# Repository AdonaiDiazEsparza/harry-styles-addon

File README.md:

# The harry styles Addon
This is a little project created for fun and love, since time ago a met a person who likes Harry Styles and an appreciated present from me is create this addon or badge or PCB as you like to call it.

## Components Hardware

| Component          | Name                 |
|--------------------|----------------------|
| MCU                | Ch32v203c8t6         |
| LiPo Charger       | TP4050/TC4050        | 
| USB Conector       | USB-C 16 pin         |
| BATTERY            | LiPo JST connector   |

## Firmware
By the moment there's no firmware programmed, it is a PoC and when the hardware will be finished, the programming will begin.

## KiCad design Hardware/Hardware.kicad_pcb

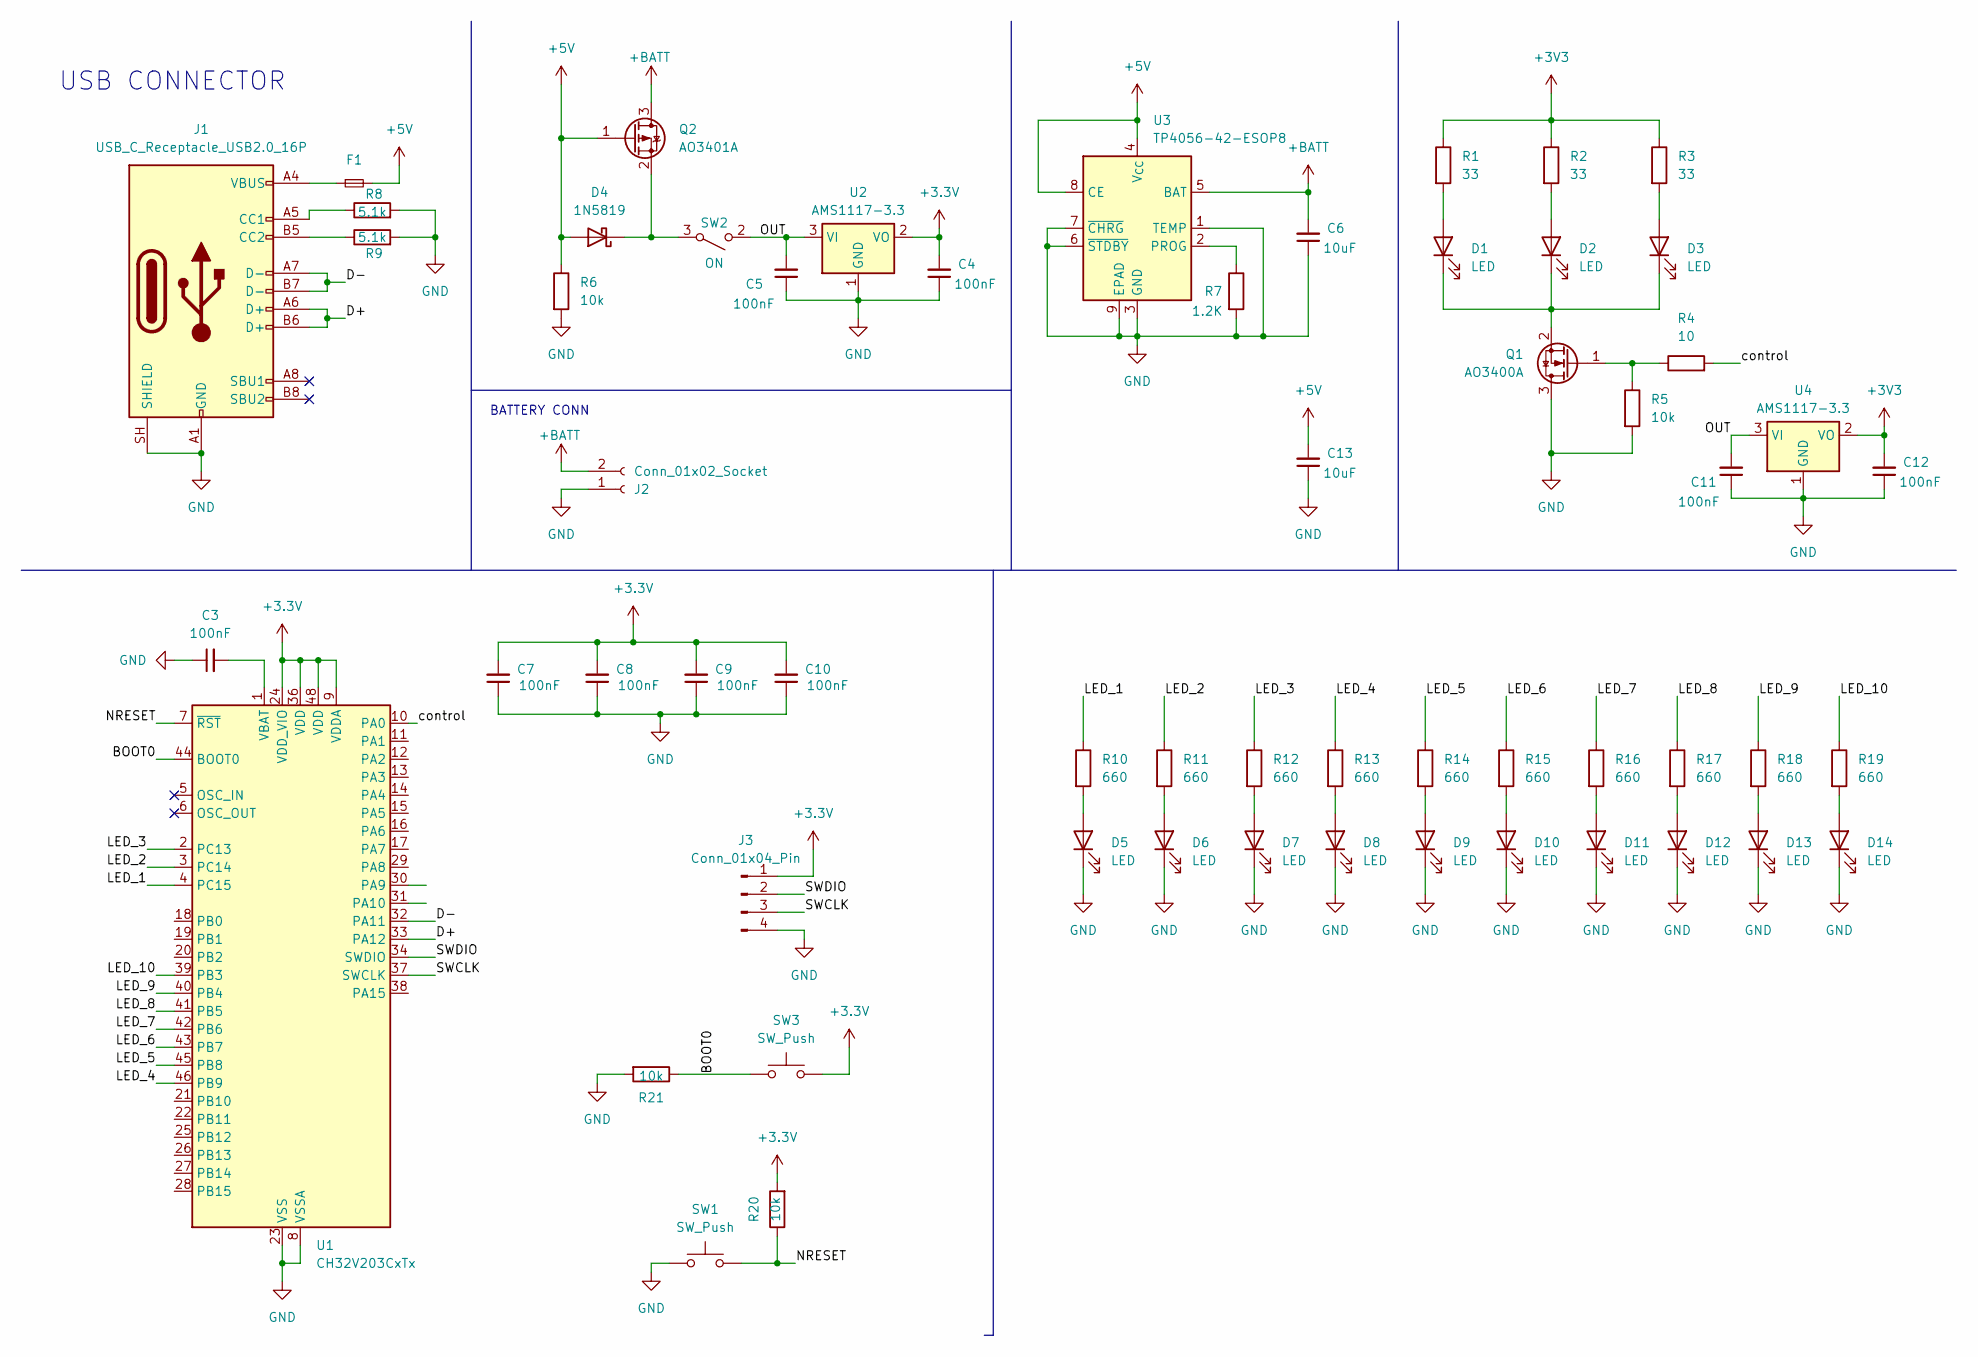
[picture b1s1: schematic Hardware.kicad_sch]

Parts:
C3, C4, C5, C7, C8, C9, C10, C11, C12: 100nF; C_0805_2012Metric
C6, C13: 10uF; C_0805_2012Metric
D1, D2, D3: LED; PinHeader_1x02_P2.54mm_Vertical
D4: 1N5819; D_SOD-323
D5, D6, D7, D8, D9, D10, D11, D12, D13, D14: LED; LED_0603_1608Metric
F1: Fuse_Small; Fuse_0603_1608Metric
J1: USB_C_Receptacle_USB2.0_16P; USB_C_Receptacle_Palconn_UTC16-G
J2: Conn_01x02_Socket; JST_PH_S2B-PH-SM4-TB_1x02-1MP_P2.00mm_Horizontal
J3: Conn_01x04_Pin; PinHeader_1x04_P2.54mm_Vertical
Q1: AO3400A; SOT-23
Q2: AO3401A; SOT-23
R1, R2, R3: 33; R_0805_2012Metric
R4: 10; R_0805_2012Metric
R5, R6, R20, R21: 10k; R_0805_2012Metric
R7: 1.2K; R_0805_2012Metric
R8, R9: 5.1k; R_0805_2012Metric
R10, R11, R12, R13, R14, R15, R16, R17, R18, R19: 660; R_0805_2012Metric
SW1, SW3: SW_Push; SW_SPST_PTS810
SW2: ON; SW_SPDT_Shouhan_MSK12C02; LCSC# C431540
U1: CH32V203CxTx; LQFP-48_7x7mm_P0.5mm
U2, U4: AMS1117-3.3; SOT-223-3_TabPin2
U3: TP4056-42-ESOP8; SOIC-8-1EP_3.9x4.9mm_P1.27mm_EP2.41x3.3mm_ThermalVias

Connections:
+3.3V: C4.2, C7.2, C8.2, C9.2, C10.2, J3.1, R20.2, SW3.2, U1.9 (VDDA), U1.24 (VDD_VIO), U1.36 (VDD), U1.48 (VDD), U2.2 (VO)
+3V3: C12.2, R1.1, R2.1, R3.1, U4.2 (VO)
+5V: C13.2, D4.2 (A), F1.2, Q2.1 (G), R6.1, U3.4 (V_{CC}), U3.8 (CE)
+BATT: C6.2, J2.2, Q2.3 (D), U3.5 (BAT)
/BOOT0: R21.1, SW3.1, U1.44 (BOOT0)
/D+: J1.A6 (D+), J1.B6 (D+), U1.33 (PA12)
/D-: J1.A7 (D-), J1.B7 (D-), U1.32 (PA11)
/LED_1: R10.1, U1.4 (PC15)
/LED_2: R11.1, U1.3 (PC14)
/LED_3: R12.1, U1.2 (PC13)
/LED_4: R13.1, U1.46 (PB9)
/LED_5: R14.1, U1.45 (PB8)
/LED_6: R15.1, U1.43 (PB7)
/LED_7: R16.1, U1.42 (PB6)
/LED_8: R17.1, U1.41 (PB5)
/LED_9: R18.1, U1.40 (PB4)
/LED_10: R19.1, U1.39 (PB3)
/NRESET: R20.1, SW1.2, U1.7 (~RST)
/OUT: C5.2, C11.2, SW2.2 (B), U2.3 (VI), U4.3 (VI)
/SWCLK: J3.3, U1.37 (SWCLK)
/SWDIO: J3.2, U1.34 (SWDIO)
/control: R4.2, U1.10 (PA0)
GND: C3.1, C4.1, C5.1, C6.1, C7.1, C8.1, C9.1, C10.1, C11.1, C12.1, C13.1, D5.1 (K), D6.1 (K), D7.1 (K), D8.1 (K), D9.1 (K), D10.1 (K), D11.1 (K), D12.1 (K), D13.1 (K), D14.1 (K), J1.A1 (GND), J1.A12 (GND), J1.B1 (GND), J1.B12 (GND), J1.SH (SHIELD), J2.1, J3.4, Q1.3 (D), R5.2, R6.2, R7.2, R8.2, R9.2, R21.2, SW1.1, U1.8 (VSSA), U1.23 (VSS), U1.35 (VSS), U1.47 (VSS), U2.1 (GND), U3.1 (TEMP), U3.3 (GND), U3.6 (~STDBY), U3.7 (~CHRG), U3.9 (EPAD), U4.1 (GND)
unnamed: D1.2 (A), R1.2
unnamed: D1.1 (K), D2.1 (K), D3.1 (K), Q1.2 (S)
unnamed: D2.2 (A), R2.2
unnamed: D3.2 (A), R3.2
unnamed: D4.1 (K), Q2.2 (S), SW2.3 (A)
unnamed: D5.2 (A), R10.2
unnamed: D6.2 (A), R11.2
unnamed: D7.2 (A), R12.2
unnamed: D8.2 (A), R13.2
unnamed: D9.2 (A), R14.2
unnamed: D10.2 (A), R15.2
unnamed: D11.2 (A), R16.2
unnamed: D12.2 (A), R17.2
unnamed: D13.2 (A), R18.2
unnamed: D14.2 (A), R19.2
unnamed: F1.1, J1.A4 (VBUS), J1.A9 (VBUS), J1.B4 (VBUS), J1.B9 (VBUS)
unnamed: J1.A5 (CC1), R8.1
unnamed: J1.B5 (CC2), R9.1
unnamed: Q1.1 (G), R4.1, R5.1
unnamed: C3.2, U1.1 (VBAT)
unnamed: R7.1, U3.2 (PROG)

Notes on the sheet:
USB CONNECTOR
BATTERY CONN

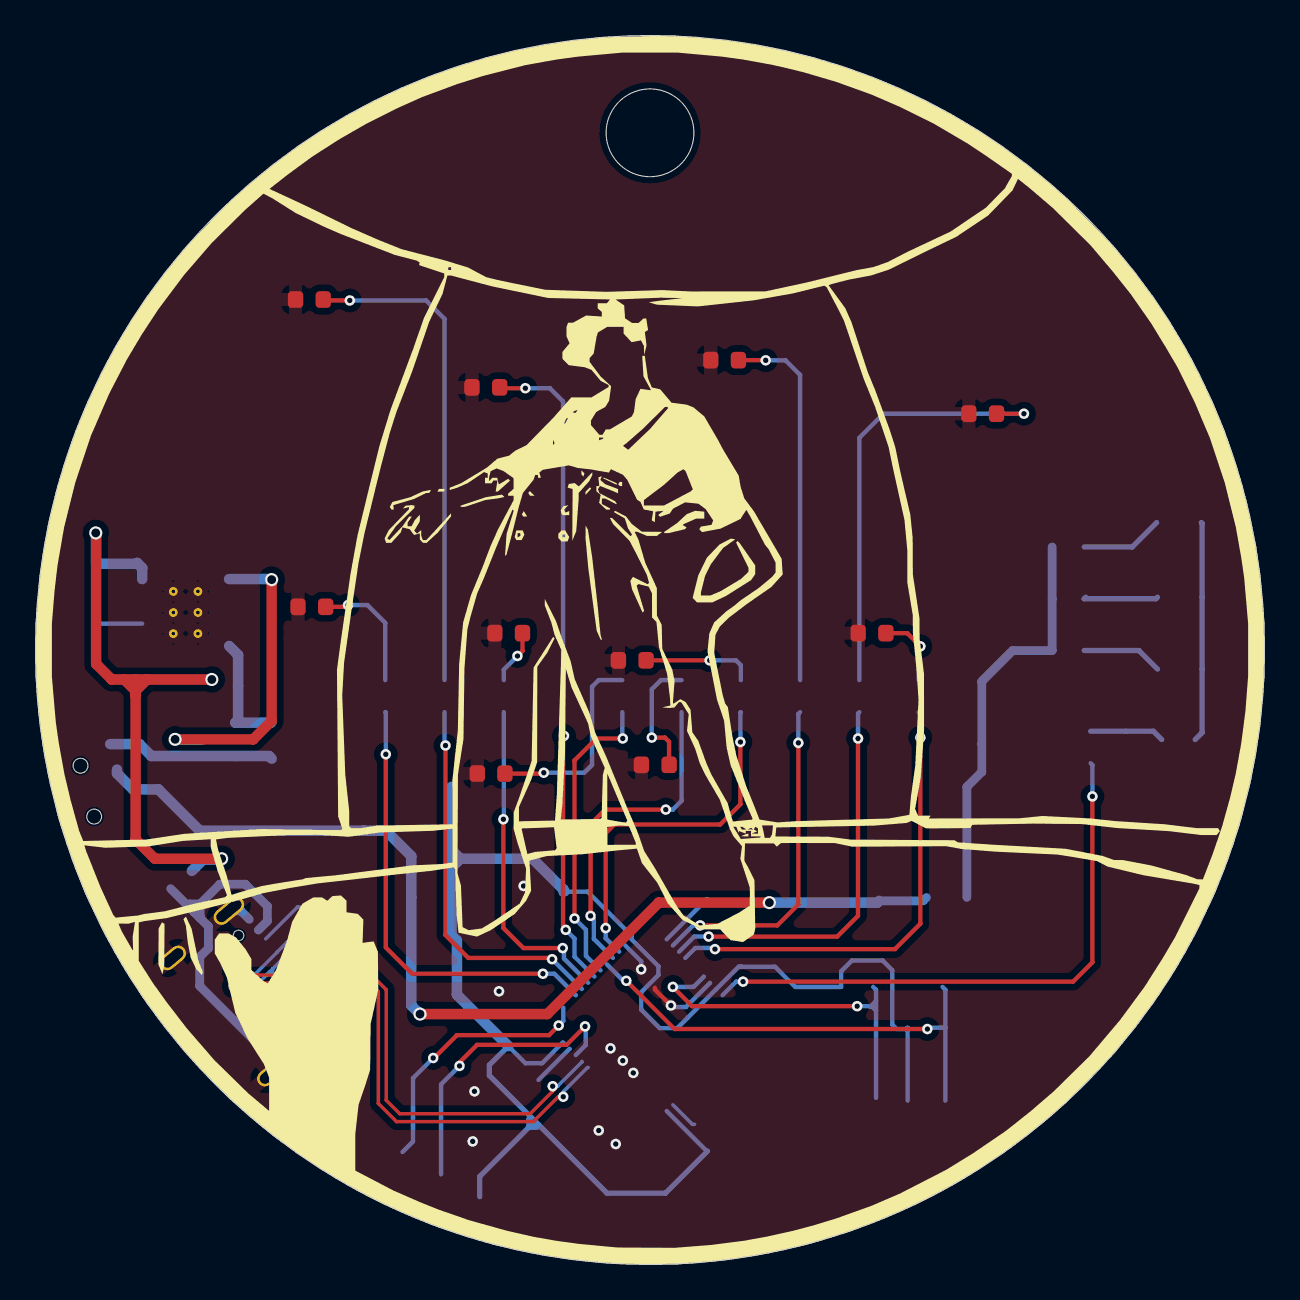
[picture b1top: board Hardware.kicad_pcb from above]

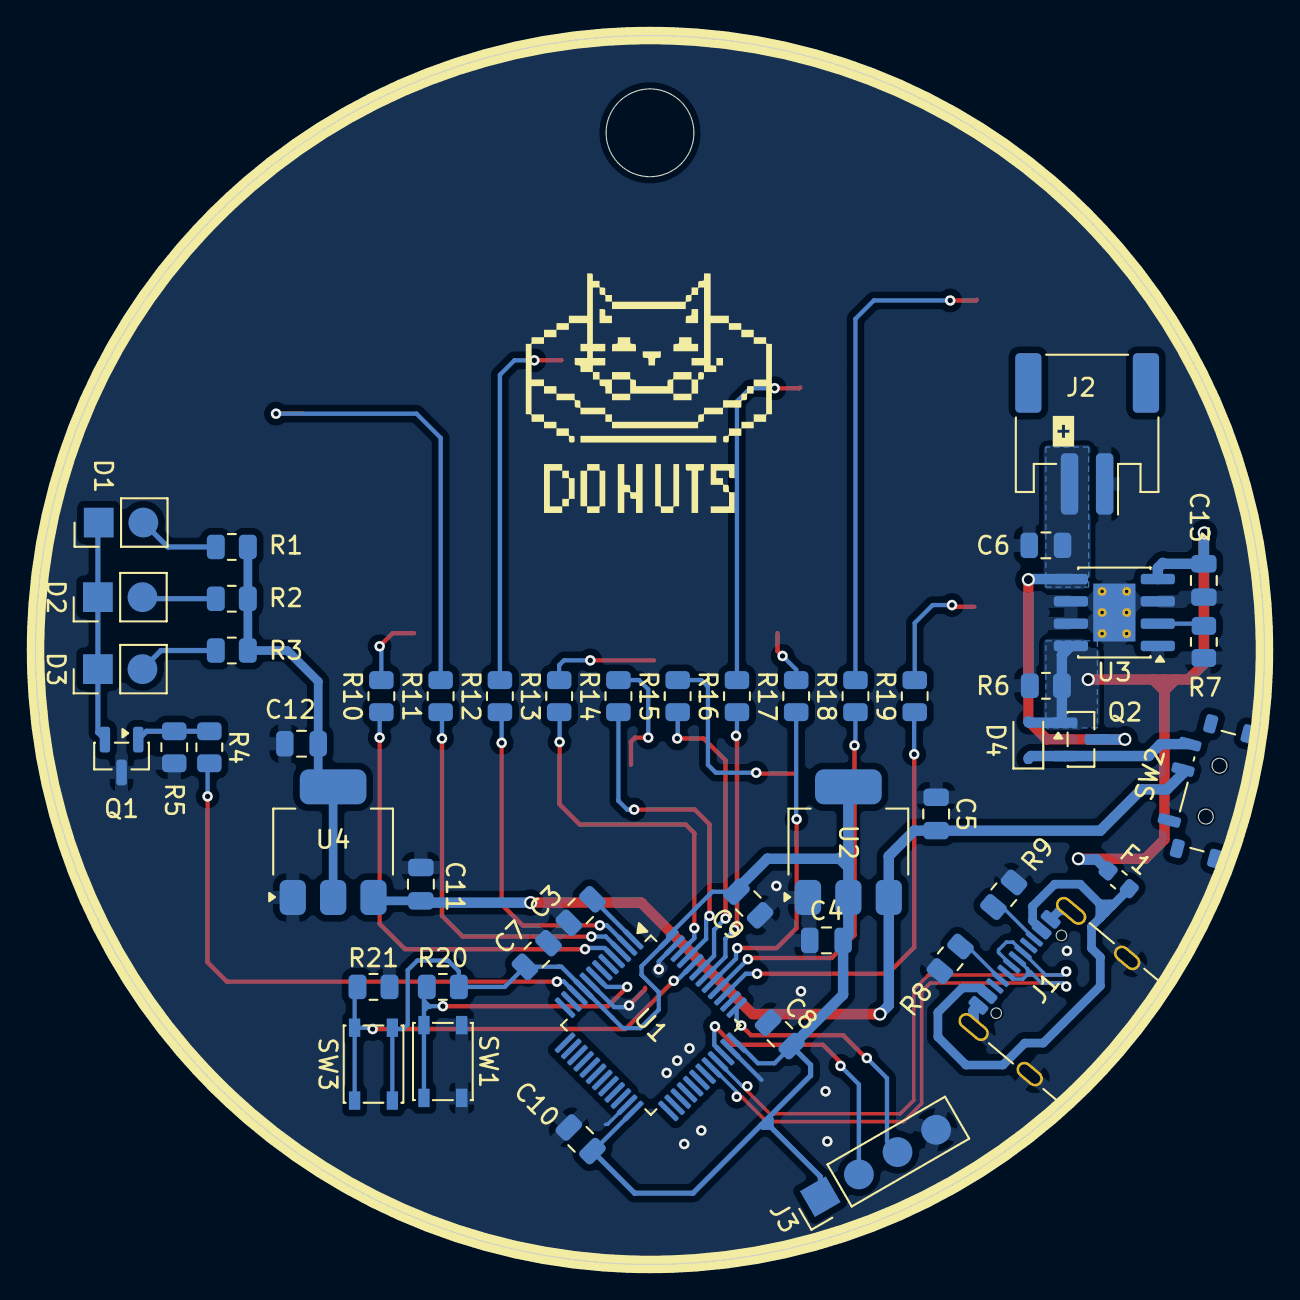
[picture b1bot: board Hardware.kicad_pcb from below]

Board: 2 copper layers, 70.0 x 70.0 mm, 60 parts (50 on the bottom side), 44 nets.

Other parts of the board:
kibuzzard-6AC594A8: G***; kibuzzard-6AC594A8
